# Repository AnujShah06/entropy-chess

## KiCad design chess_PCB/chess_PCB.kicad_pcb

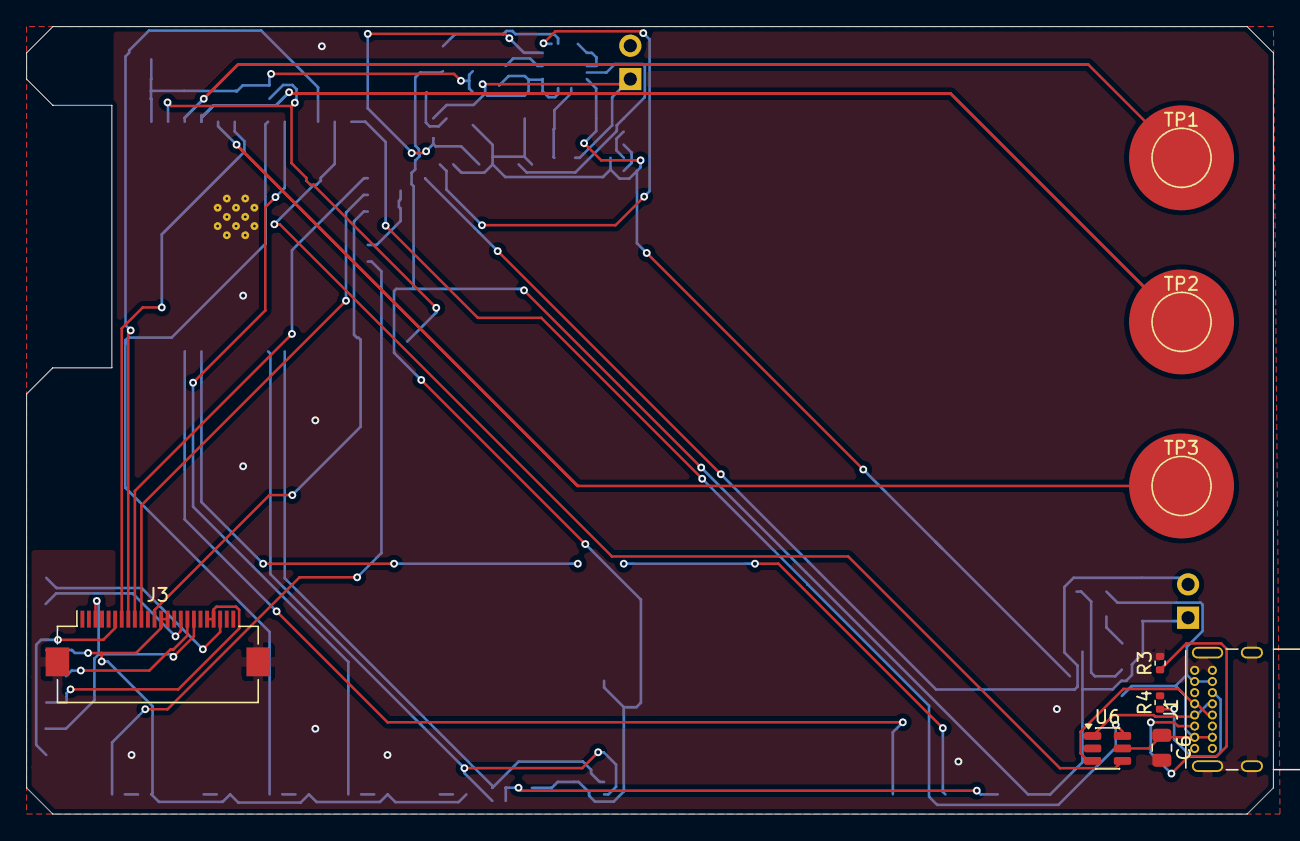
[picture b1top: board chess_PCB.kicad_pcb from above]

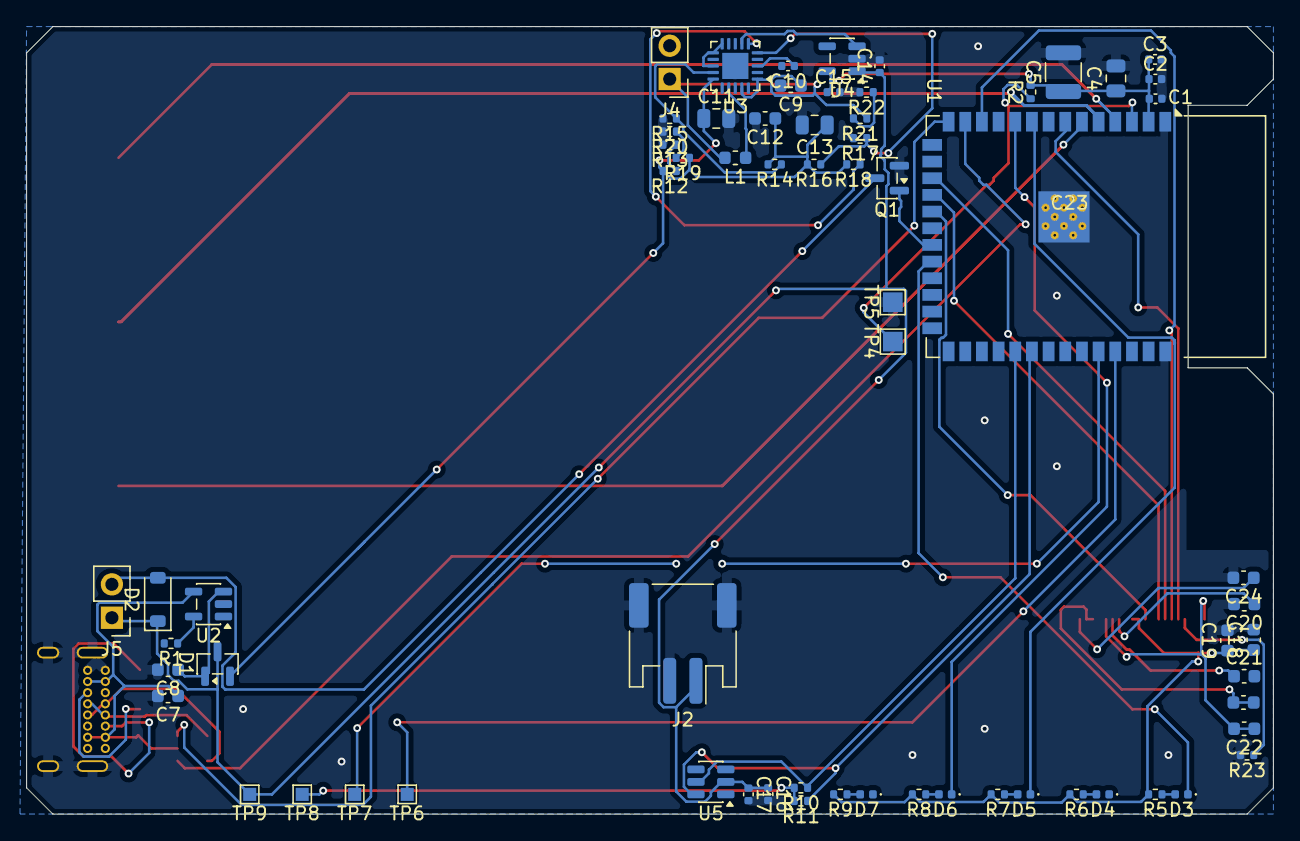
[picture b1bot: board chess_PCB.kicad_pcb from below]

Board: 2 copper layers, 95.0 x 60.0 mm, 76 parts (67 on the bottom side), 56 nets.

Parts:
C1, C2, C3, C17: 100nF; C_0402_1005Metric
C4, C6, C13: 10uF; C_0805_2012Metric
C5: 100uF; C_1210_3225Metric
C7, C8, C9, C12: 4.7uF; C_0603_1608Metric
C10: 10nF; C_0402_1005Metric
C11: 22uF; C_0805_2012Metric
C14, C15, C16: 1uF; C_0402_1005Metric
C18, C19, C20, C21, C22, C23, C24: 1uF; C_0603_1608Metric
D1: BAT54S; SOT-23
D2: 1N4148W; D_SOD-123
D3, D4: Red; LED_0402_1005Metric
D5: Yellow; LED_0402_1005Metric
D6, D7: Green; LED_0402_1005Metric
J1: USB-C 16P SMD; USB_C_Receptacle_GCT_USB4085
J2: JST-PH 2P SMD; JST_PH_S2B-PH-SM4-TB_1x02-1MP_P2.00mm_Horizontal
J3: FPC 24P 0.5mm; Hirose_FH12-24S-0.5SH_1x24-1MP_P0.50mm_Horizontal
J4: Solar Cell Pads; PinHeader_1x02_P2.54mm_Vertical
J5: ERM Motor Pads; PinHeader_1x02_P2.54mm_Vertical
L1: 22uH; L_0603_1608Metric
Q1: 2N7002; SOT-23
R1: 2k; R_0402_1005Metric
R2, R23: 10k; R_0402_1005Metric
R3, R4: 5.1k; R_0402_1005Metric
R5, R6, R7, R8, R9: 1k; R_0402_1005Metric
R10, R11: 4.7k; R_0402_1005Metric
R12: 5.49M; R_0402_1005Metric
R13: 3.39M; R_0402_1005Metric
R14: 5.65M; R_0402_1005Metric
R15: 4.42M; R_0402_1005Metric
R16: 5.07M; R_0402_1005Metric
R17: 3.69M; R_0402_1005Metric
R18: 6.04M; R_0402_1005Metric
R19: 7.50M; R_0402_1005Metric
R20: 3.32M; R_0402_1005Metric
R21, R22: 10M; R_0402_1005Metric
TP1: Touch UP; TestPoint_Pad_D4.0mm
TP2: Touch SELECT; TestPoint_Pad_D4.0mm
TP3: Touch DOWN; TestPoint_Pad_D4.0mm
TP4: RST_BRIDGE_A; TestPoint_Pad_1.5x1.5mm
TP5: RST_BRIDGE_B; TestPoint_Pad_1.5x1.5mm
TP6: TP_TX; TestPoint_Pad_1.0x1.0mm
TP7: TP_RX; TestPoint_Pad_1.0x1.0mm
TP8: TP_3V3; TestPoint_Pad_1.0x1.0mm
TP9: TP_VBAT; TestPoint_Pad_1.0x1.0mm
U1: ESP32-S3-WROOM-2-N16R8; ESP32-S3-WROOM-1
U2: MCP73832T-2ACI/OT; SOT-23-5
U3: BQ25570RGRR; QFN-20-1EP_3.5x3.5mm_P0.5mm_EP2x2mm
U4: XC6220B331MR-G; SOT-23-5
U5: MAX17048G+T10; SOT-23-6
U6: USBLC6-2SC6; SOT-23-6

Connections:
+3V3: C1.1, C2.1, C3.1, C4.1, C5.1, C15.1, C18.1, C19.1, J3.13 (VDDIO), J3.14 (VCI), R2.2, R5.2, R6.2, R7.2, R8.2, R9.2, R10.2, R11.2, TP8.1, U1.2 (3V3), U4.5 (VOUT)
BQ_LBOOST: L1.1, U3.17 (LBOOST)
BQ_OK_HYST: R18.1, U3.6 (OK_HYST)
BQ_OK_PROG: R16.1, R17.1, U3.5 (OK_PROG)
BQ_VBAT_OV: R12.1, R13.1, U3.12 (VBAT_OV)
BQ_VBAT_UV: R14.1, R15.1, U3.14 (VBAT_UV)
BQ_VOC_SAMP: R21.2, R22.1, U3.2 (VOC_SAMP)
BQ_VOUT_SET: R19.2, R20.1, U3.9 (VOUT_SET)
BQ_VRDIV: U3.4 (VRDIV), U3.16 (VRDIV2)
BQ_VREF_SAMP: C10.1, U3.3 (VREF_SAMP)
CC1: J1.A5 (CC1), R3.1
CC2: J1.B5 (CC2), R4.1
CHG_PROG: R1.1, U2.5 (PROG)
DEBUG_RX: TP7.1, U1.36 (RXD0)
DEBUG_TX: TP6.1, U1.37 (TXD0)
EP_BS: J3.6 (BS), R23.1
EP_BUSY: J3.7 (BUSY), U1.7 (IO7)
EP_CS: J3.10 (CS_N), U1.18 (IO10)
EP_DC: J3.9 (DC), U1.17 (IO9)
EP_MOSI: J3.12 (SDA), U1.19 (IO11)
EP_RST: J3.8 (RES_N), U1.12 (IO8)
EP_SCK: J3.11 (SCL), U1.20 (IO12)
EP_VCOM: C24.1, J3.22 (VCOM)
EP_VDD: C20.1, J3.16 (VDD)
EP_VGH_VGL: C23.1, C23.2, J3.20 (VGL), J3.21 (VGH)
EP_VPP: C21.1, J3.17 (VPP)
EP_VSH_VSL: C22.1, C22.2, J3.3 (VSH), J3.18 (VSL)
ESP_EN: R2.1, TP4.1, U1.3 (EN)
GND: C1.2, C2.2, C3.2, C4.2, C5.2, C6.2, C7.2, C8.2, C9.2, C10.2, C11.2, C12.2, C13.2, C14.2, C15.2, C16.2, C17.2, C18.2, C19.2, C20.2, C21.2, C24.2, J1.A1 (GND), J1.A12 (GND), J1.B1 (GND), J1.B12 (GND), J1.SH (SHIELD), J2.2 (GND), J2.MP, J3.4 (TSCL), J3.5 (TSDA), J3.15 (VSS), J3.24 (VSS2), J3.MP, J4.2 (SOL_MINUS), Q1.2 (S), R1.2, R3.2, R4.2, R13.2, R15.2, R17.2, R20.2, R22.2, R23.2, TP5.1, U1.1 (GND), U1.40 (GND), U1.41 (EPAD), U2.2 (GND), U3.18 (VSS), U3.20 (EN), U3.21 (EPAD), U4.2 (GND), U5.1 (QSTRT), U5.3 (GND), U6.2 (GND)
HAPTIC_GATE: Q1.1 (G), U1.21 (IO13)
I2C_SCL: R11.1, U1.32 (IO39), U5.6 (SCL)
I2C_SDA: R10.1, U1.31 (IO38), U5.5 (SDA)
LED1_NET: D3.1 (K), U1.22 (IO14)
LED1_R: D3.2 (A), R5.1
LED2_NET: D4.1 (K), U1.8 (IO15)
LED2_R: D4.2 (A), R6.1
LED3_NET: D5.1 (K), U1.9 (IO16)
LED3_R: D5.2 (A), R7.1
LED4_NET: D6.1 (K), U1.10 (IO17)
LED4_R: D6.2 (A), R8.1
LED5_NET: D7.1 (K), U1.11 (IO18)
LED5_R: D7.2 (A), R9.1
MOTOR_NEG: D2.2 (A), J5.2 (MOT_MINUS), Q1.3 (D)
SOL_CHG: C11.1, C12.1, C13.1, D1.2 (A2), R12.2, R14.2, R16.2, R18.2, R19.1, U3.10 (VOUT_EN), U3.11 (VOUT), U3.13 (VBAT), U3.15 (VSTOR)
TOUCH_DN: TP3.1, U1.6 (IO6)
TOUCH_SEL: TP2.1, U1.5 (IO5)
TOUCH_UP: TP1.1, U1.4 (IO4)
USB_CHG: C8.1, D1.1 (A1), U2.3 (VBAT)
USB_DM: J1.A7 (DN1), J1.B7 (DN2), U6.3 (IO2)
USB_DM_PROT: U1.13 (IO19), U6.4 (IO2_P)
USB_DP: J1.A6 (DP1), J1.B6 (DP2), U6.1 (IO1)
USB_DP_PROT: U1.14 (IO20), U6.6 (IO1_P)
VBAT: C14.1, C16.1, C17.1, D1.3 (K), D2.1 (K), J2.1 (VBAT), J5.1 (MOT_PLUS), TP9.1, U4.1 (VIN), U5.2 (VDD)
VBAT_OK: U3.7 (VBAT_OK), U4.3 (EN)
VBUS: C6.1, C7.1, J1.A4 (VBUS), J1.A9 (VBUS), J1.B4 (VBUS), J1.B9 (VBUS), U2.4 (VDD), U6.5 (VBUS)
VSOLAR: C9.1, J4.1 (SOL_PLUS), L1.2, R21.1, U3.1 (VIN_DC), U3.19 (VIN_DC)

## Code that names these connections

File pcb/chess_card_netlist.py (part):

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    ]),

    # ---------- E-paper SPI + control ----------
    ("EP_BUSY", [("U1", "7"),  ("J3", "7")]),    # GPIO7
    ("EP_RST",  [("U1", "12"), ("J3", "8")]),    # GPIO8
    ("EP_DC",   [("U1", "17"), ("J3", "9")]),    # GPIO9
    ("EP_CS",   [("U1", "18"), ("J3", "10")]),   # GPIO10
    ("EP_MOSI", [("U1", "19"), ("J3", "12")]),   # GPIO11 -> SDA
    ("EP_SCK",  [("U1", "20"), ("J3", "11")]),   # GPIO12 -> SCL

    # ---------- E-paper internal supply pins ----------
    ("EP_VDD",  [("J3", "16"), ("C20", "1")]),  # Internal logic supply
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    ]),

    # ---------- Charge level LEDs ----------
    ("LED1_NET", [("U1", "22"), ("D3", "1")]),  # GPIO14 -> LED cathode
    ("LED2_NET", [("U1", "8"),  ("D4", "1")]),  # GPIO15 -> LED cathode
    ("LED3_NET", [("U1", "9"), ("D5", "1")]),  # GPIO16 -> LED cathode
    ("LED4_NET", [("U1", "10"), ("D6", "1")]),  # GPIO17 -> LED cathode
    ("LED5_NET", [("U1", "11"), ("D7", "1")]),  # GPIO18 -> LED cathode

    ("LED1_R",   [("D3", "2"), ("R5", "1")]),
    ("LED2_R",   [("D4", "2"), ("R6", "1")]),
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
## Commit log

2026-04-20 cleaned git history
2026-05-01 removed old code
2026-05-01 file fixes
2026-05-01 updated specs
2026-05-01 reformatted folders
2026-05-01 vqvae & energy constructor
2026-05-01 Created dataloader
2026-05-01 Fixed path
2026-05-01 removed vqvae, custom no-downsample encoder
2026-05-01 removed vqvae, added custom encoder
2026-05-01 Precompute dataset + fixed loader
2026-05-01 training stage 1
2026-05-01 working train1
2026-05-03 chess PCB
2026-05-03 updated pcb
2026-05-04 pcb placement
2026-05-04 final PCB
